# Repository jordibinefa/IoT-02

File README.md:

# IoT-02
Codes and schematics of IoT-02 board

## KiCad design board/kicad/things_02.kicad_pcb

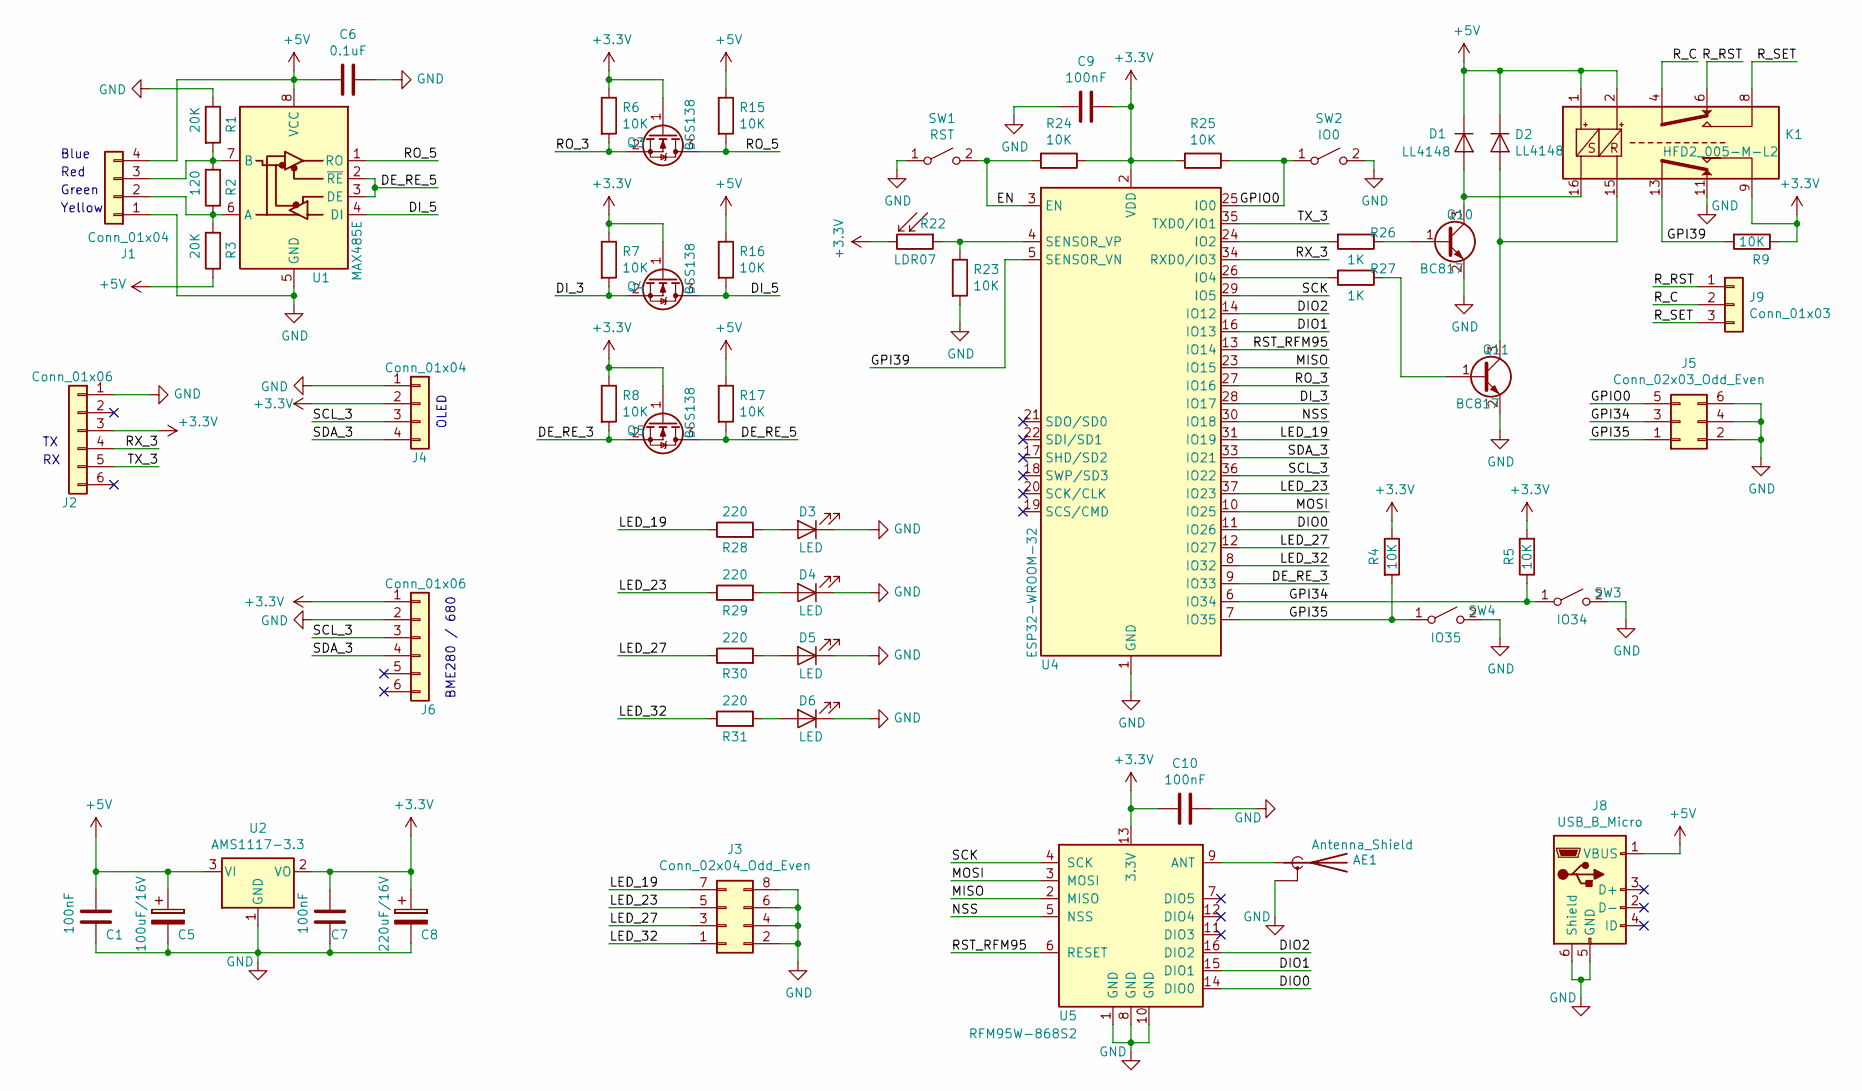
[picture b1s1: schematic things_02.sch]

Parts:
AE1: Antenna_Shield; U.FL_Molex_MCRF_73412-0110_Vertical
C1, C7, C9, C10: 100nF; C_1206_3216Metric
C5: 100uF/16V; CP_Elec_5x5.9
C6: 0.1uF; C_1206_3216Metric
C8: 220uF/16V; CP_Elec_5x5.9
D1, D2: LL4148; D_1206_3216Metric_Pad1.42x1.75mm_HandSolder
D3, D4, D5, D6: LED; LED_1206_3216Metric_Pad1.42x1.75mm_HandSolder
J1: Conn_01x04; JST_EH_B04B-EH-A_1x04_P2.50mm_Vertical
J2, J6: Conn_01x06; PinSocket_1x06_P2.54mm_Vertical
J3: Conn_02x04_Odd_Even; PinHeader_2x04_P2.54mm_Vertical
J4: Conn_01x04; PinSocket_1x04_P2.54mm_Vertical
J5: Conn_02x03_Odd_Even; PinSocket_2x03_P2.54mm_Vertical
J8: USB_B_Micro; USB_Micro-B_Amphenol_10103594-0001LF_Horizontal
J9: Conn_01x03; TerminalBlock_bornier-3_P5.08mm
K1: HFD2_005-M-L2
Q3, Q4, Q5: BSS138; SOT-23
Q10, Q11: BC817; SOT-23
R1, R3: 20K; R_0805_2012Metric_Pad1.15x1.40mm_HandSolder
R2: 120; R_0805_2012Metric_Pad1.15x1.40mm_HandSolder
R4, R5, R6, R7, R8, R9, R15, R16, R17, R23, R24, R25: 10K; R_0805_2012Metric_Pad1.15x1.40mm_HandSolder
R22: LDR07; R_LDR_5.1x4.3mm_P3.4mm_Vertical
R26, R27: 1K; R_0805_2012Metric_Pad1.15x1.40mm_HandSolder
R28, R29, R30, R31: 220; R_0805_2012Metric_Pad1.15x1.40mm_HandSolder
SW1: RST; SW_SPST_EVQPE1
SW2: IO0; SW_SPST_EVQPE1
SW3: IO34; SW_SPST_EVQPE1
SW4: IO35; SW_SPST_EVQPE1
U1: MAX485E; SOIC-8_3.9x4.9mm_P1.27mm
U2: AMS1117-3.3; SOT-223-3_TabPin2
U4: ESP32-WROOM-32
U5: RFM95W-868S2; HOPERF_RFM9XW_SMD

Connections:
+3V3: C7.1, C8.1, C9.1, C10.2, J2.3, J4.2, J6.1, K1.9, Q3.1 (G), Q4.1 (G), Q5.1 (G), R4.1, R5.2, R6.1, R7.1, R8.1, R9.1, R22.2, R24.1, R25.2, U2.2 (VO), U4.2 (VDD), U5.13 (3.3V)
+5V: C1.1, C5.1, C6.2, D1.1 (K), D2.1 (K), J1.4, J8.1 (VBUS), K1.1, K1.2, R3.1, R15.1, R16.1, R17.1, U1.8 (VCC), U2.3 (VI)
/DE_RE_3: Q5.2 (S), R8.2, U4.9 (IO33)
/DE_RE_5: Q5.3 (D), R17.2, U1.2 (~RE), U1.3 (DE)
/DIO0: U4.11 (IO26), U5.14 (DIO0)
/DIO1: U4.16 (IO13), U5.15 (DIO1)
/DIO2: U4.14 (IO12), U5.16 (DIO2)
/DI_3: Q4.2 (S), R7.2, U4.28 (IO17)
/DI_5: Q4.3 (D), R16.2, U1.4 (DI)
/EN: R24.2, SW1.2 (B), U4.3 (EN)
/GPI34: J5.3, R5.1, SW3.1 (A), U4.6 (IO34)
/GPI35: J5.1, R4.2, SW4.1 (A), U4.7 (IO35)
/GPI39: K1.13, R9.2, U4.5 (SENSOR_VN)
/GPIO0: J5.5, R25.1, SW2.1 (A), U4.25 (IO0)
/LED_19: J3.7, R28.1, U4.31 (IO19)
/LED_23: J3.5, R29.1, U4.37 (IO23)
/LED_27: J3.3, R30.1, U4.12 (IO27)
/LED_32: J3.1, R31.1, U4.8 (IO32)
/MISO: U4.23 (IO15), U5.2 (MISO)
/MOSI: U4.10 (IO25), U5.3 (MOSI)
/NSS: U4.30 (IO18), U5.5 (NSS)
/RO_3: Q3.2 (S), R6.2, U4.27 (IO16)
/RO_5: Q3.3 (D), R15.2, U1.1 (RO)
/RST_RFM95: U4.13 (IO14), U5.6 (RESET)
/RX_3: J2.4, U4.34 (RXD0/IO3)
/R_C: J9.2, K1.4
/R_RST: J9.1, K1.6
/R_SET: J9.3, K1.8
/SCK: U4.29 (IO5), U5.4 (SCK)
/SCL_3: J4.3, J6.3, U4.36 (IO22)
/SDA_3: J4.4, J6.4, U4.33 (IO21)
/TX_3: J2.5, U4.35 (TXD0/IO1)
GND: AE1.2 (Shield), C1.2, C5.2, C6.1, C7.2, C8.2, C9.2, C10.1, D3.1 (K), D4.1 (K), D5.1 (K), D6.1 (K), J1.1, J2.1, J3.2, J3.4, J3.6, J3.8, J4.1, J5.2, J5.4, J5.6, J6.2, J8.5 (GND), J8.6 (Shield), K1.11, Q10.2 (E), Q11.2 (E), R1.1, R23.2, SW1.1 (A), SW2.2 (B), SW3.2 (B), SW4.2 (B), U1.5 (GND), U2.1 (GND), U4.1 (GND), U4.15 (GND), U4.38 (GND), U5.1 (GND), U5.8 (GND), U5.10 (GND)
unnamed: AE1.1 (A), U5.9 (ANT)
unnamed: D1.2 (A), K1.16, Q10.3 (C)
unnamed: D2.2 (A), K1.15, Q11.3 (C)
unnamed: D3.2 (A), R28.2
unnamed: D4.2 (A), R29.2
unnamed: D5.2 (A), R30.2
unnamed: D6.2 (A), R31.2
unnamed: J1.2, R2.1, R3.2, U1.6 (A)
unnamed: J1.3, R1.2, R2.2, U1.7 (B)
unnamed: Q10.1 (B), R26.1
unnamed: Q11.1 (B), R27.1
unnamed: R22.1, R23.1, U4.4 (SENSOR_VP)
unnamed: R26.2, U4.24 (IO2)
unnamed: R27.2, U4.26 (IO4)

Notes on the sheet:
Blue
Red
Green
Yellow
OLED
BME280 / 680

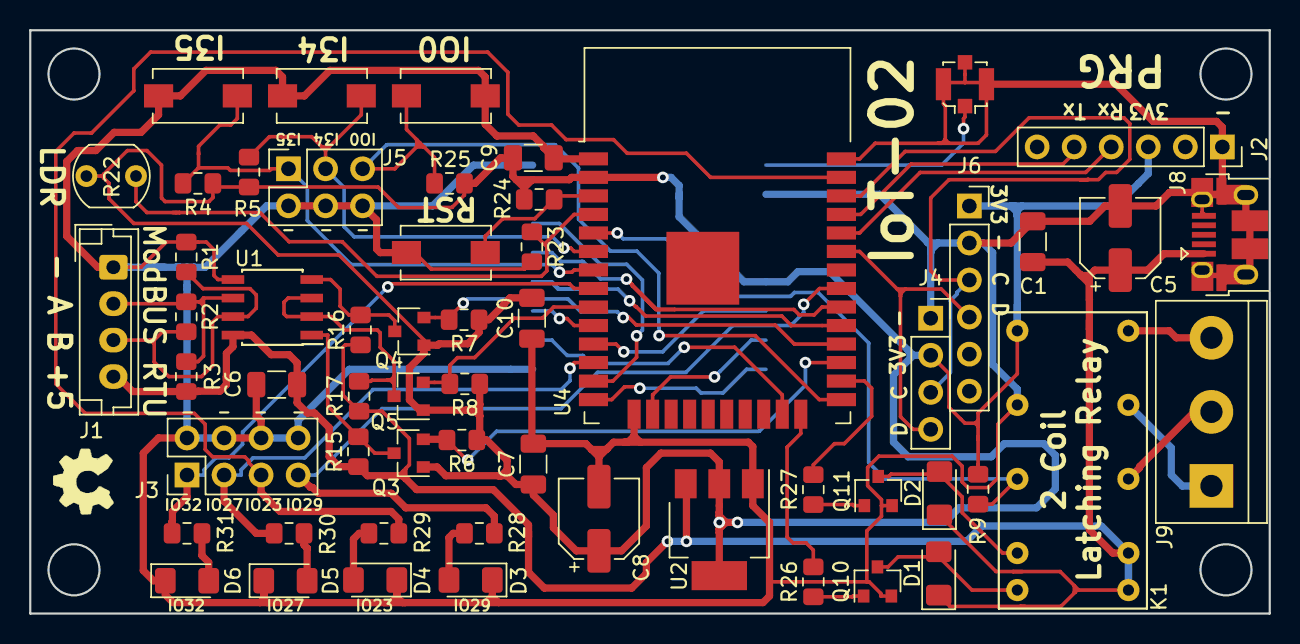
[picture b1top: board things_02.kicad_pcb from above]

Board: 2 copper layers, 85.0 x 40.0 mm, 58 parts (1 on the bottom side), 47 nets.

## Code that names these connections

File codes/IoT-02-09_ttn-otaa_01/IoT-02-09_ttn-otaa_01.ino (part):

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#define NSS_GPIO    18 /*16*/
#define RXTX_GPIO   LMIC_UNUSED_PIN
#define RESET_GPIO  14
#define DIO0_GPIO   26
#define DIO1_GPIO   13
#define DIO2_GPIO   12

const lmic_pinmap lmic_pins = {
  .nss = NSS_GPIO,
  .rxtx = RXTX_GPIO,
  .rst = RESET_GPIO,
  .dio = {DIO0_GPIO, DIO1_GPIO, DIO2_GPIO},
};
/*
  const lmic_pinmap lmic_pins = {
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
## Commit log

2024-07-05 Update IoT-02_wifiMng.cpp
    Migrating from ESP32 compiler v2 to v3
2024-07-05 Update IoT-02_wifiMng.cpp
    To be able to compile this code using new ESP32 compiler v3
2024-07-05 Update IoT-02_wifiMng.cpp
    To be able to compile using ESP32 compiler v3
